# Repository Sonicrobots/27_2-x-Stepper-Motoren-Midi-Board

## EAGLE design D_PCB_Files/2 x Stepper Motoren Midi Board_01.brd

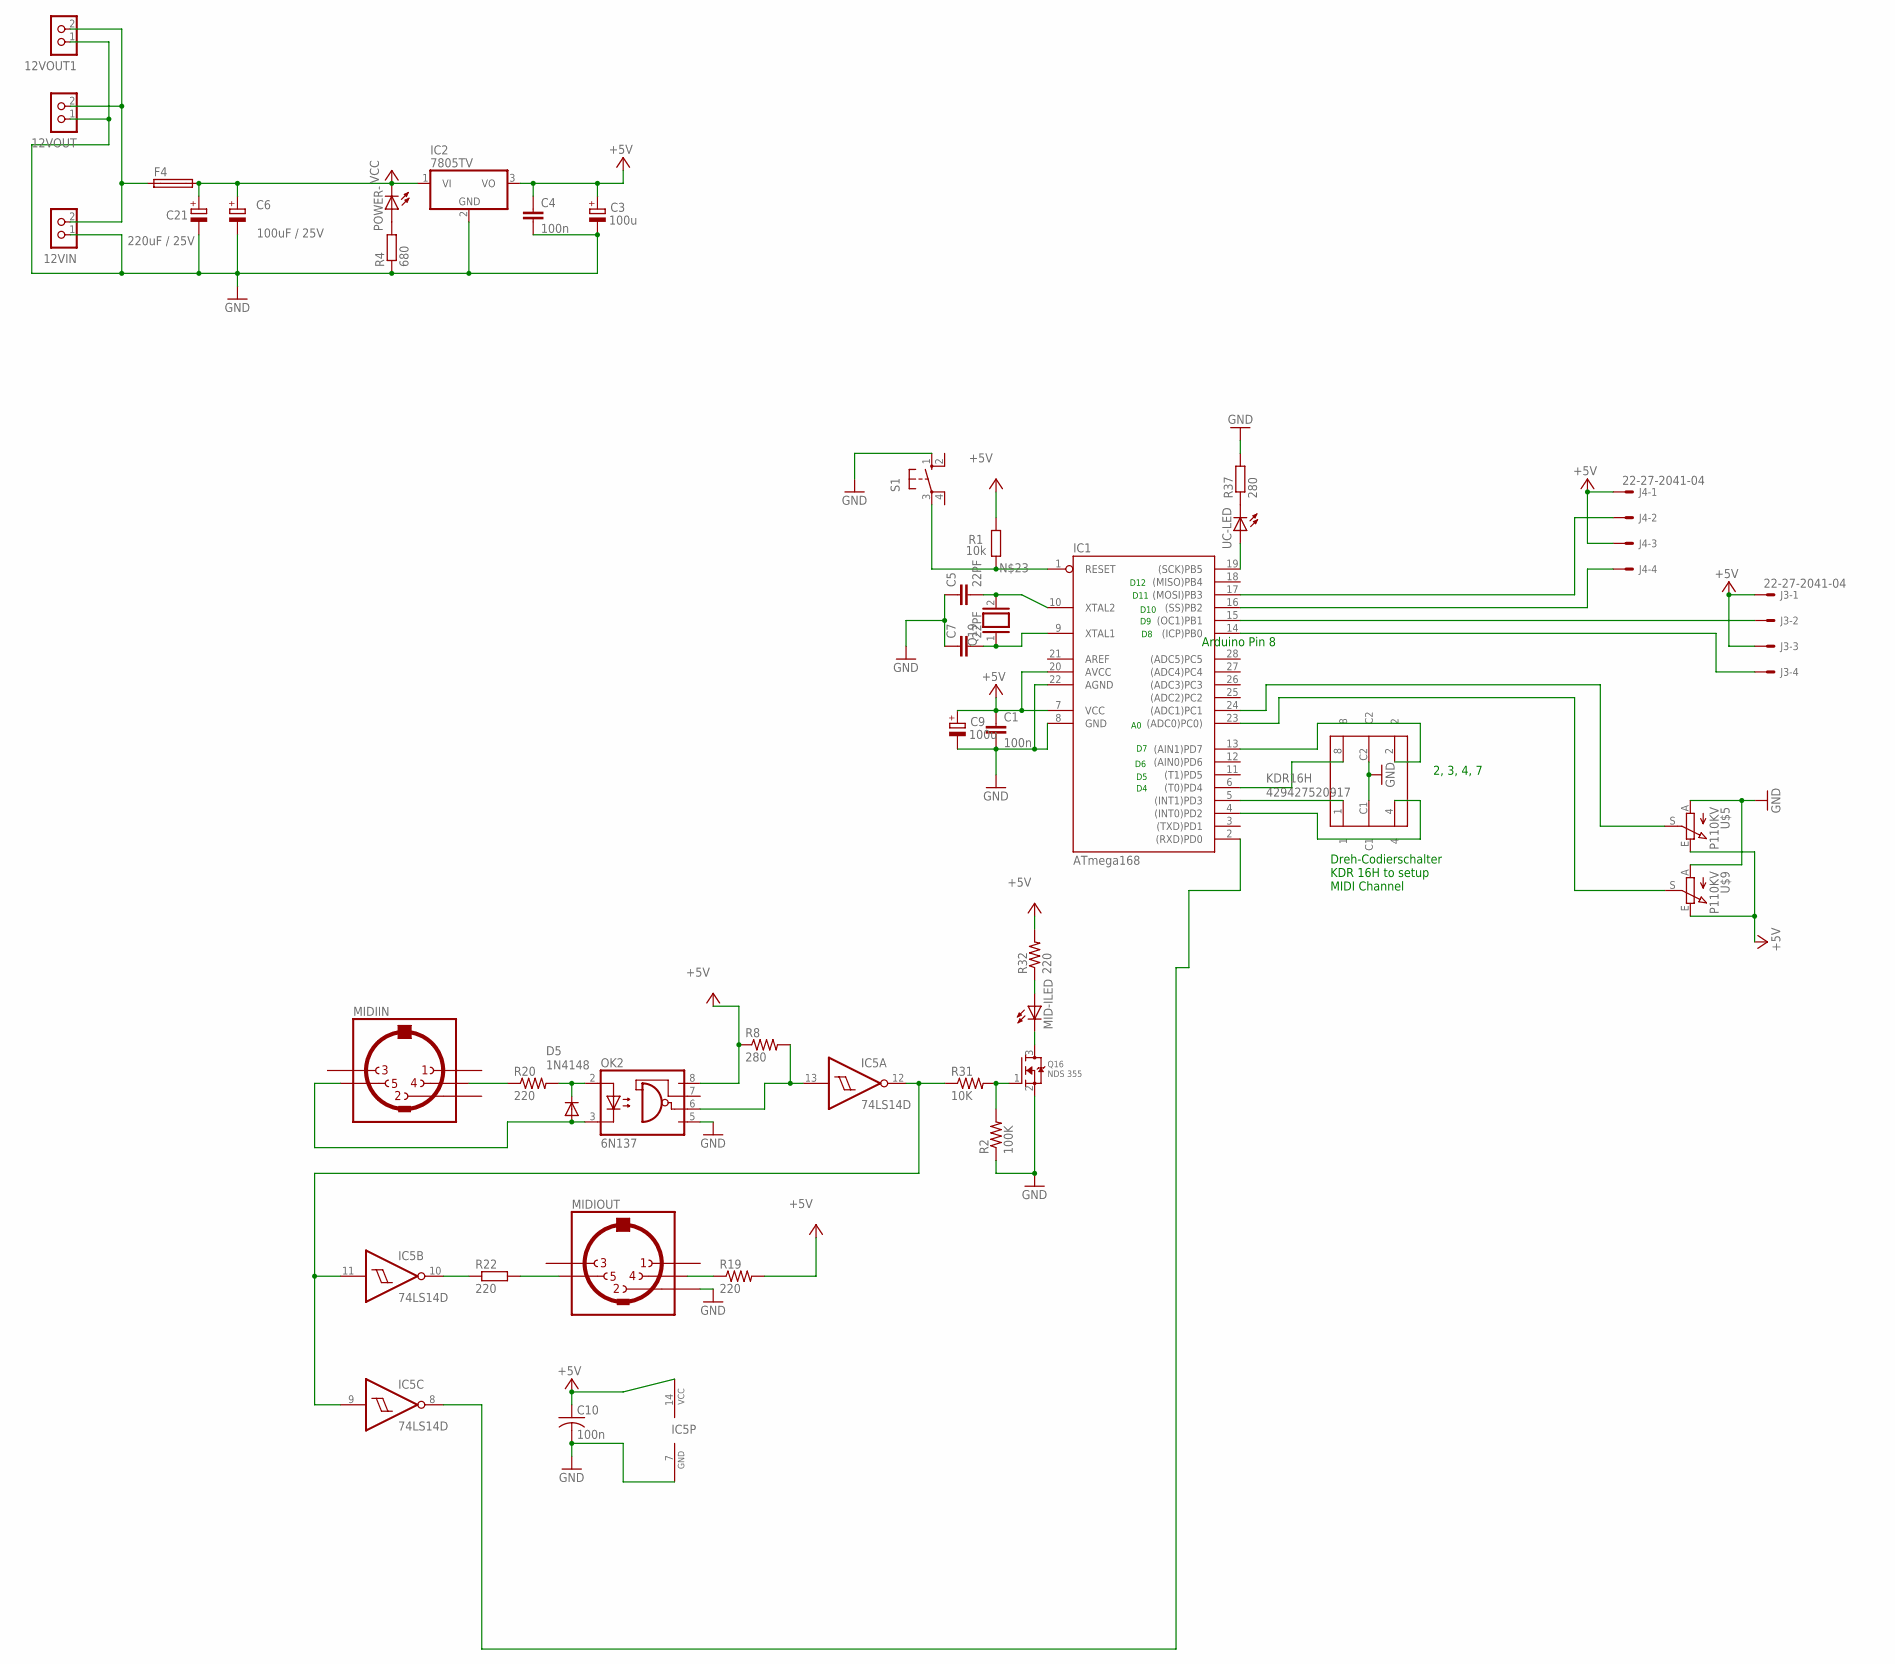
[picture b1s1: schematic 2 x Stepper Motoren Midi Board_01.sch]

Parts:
12VIN, 12VOUT, 12VOUT1: CON_TERMINAL_BLOCK_02-5MM; TERMINAL_BLOCK_2P_5
C1, C4: 100n; C0805K
C3: 100u; E2,5-7
C5, C7: 22PF; C0805
C6: 100uF / 25V; E2,5-7
C9: 100u; E2,5-6
C10: 100n; C0805
C21: 220uF / 25V; E5-8,5
D5: 1N4148; D-7.5
F4: SH22,5
IC1: ATmega168; DIL28-3
IC2: 7805TV; TO220V
IC5: 74LS14D; SO14
J3, J4: 22-27-2041-04; 6410-04
KDR16H: 429427520917
MID-ILED: LED3MM
MIDIIN: MAB5SH
MIDIOUT: MAB5SH
OK2: 6N137; DIL08; MPN 6N137
POWER-: LED3MM
Q16: NDS 355; SOT23-W
Q19: XTAL/S; QS
R1: 10k; R0805
R2: 100K; R0805W
R4: 680; R0805W
R8: 280; M0805
R19, R32: 220; R0805W
R20, R22: 220; R0805
R31: 10K; R0805W
R37: 280; R0805
S1: 10-XX; B3F-10XX
U$5, U$9: P110KV; POT-P110KV
UC-LED: LED3MM

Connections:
+5V: C1.1, C3.+, C4.1, C9.+, C10.1, IC1.7 (VCC), IC1.20 (AVCC), IC2.3 (VO), IC5.14 (VCC), J3.1, J3.3, J4.1, J4.3, OK2.8 (VCC), R1.2, R8.1, R19.2, R32.2, U$5.E, U$9.E
A1_IN: IC1.24 ((ADC1)PC1), U$5.S
A2_IN: IC1.23 ((ADC0)PC0)), U$9.S
GND: 12VIN.1, 12VOUT.1, 12VOUT1.1, C1.2, C3.-, C4.2, C5.1, C6.-, C7.1, C9.-, C10.2, C21.-, IC1.8 (GND), IC1.22 (AGND), IC2.2 (GND), IC5.7 (GND), KDR16H.C1, KDR16H.C2, MIDIOUT.2, OK2.5 (GND), Q16.2 (S), R2.1, R4.1, R37.2, S1.1 (S), U$5.A, U$9.A
MIDI_IN1: IC5.9 (I), IC5.11 (I), IC5.12 (O), R31.1
unnamed: IC1.15 ((OC1)PB1), J3.2
unnamed: IC1.14 ((ICP)PB0), J3.4
unnamed: POWER-.A, R4.2
unnamed: IC1.16 ((SS)PB2), J4.4
unnamed: 12VIN.2, 12VOUT.2, 12VOUT1.2, F4.1
unnamed: C7.2, IC1.9 (XTAL1), Q19.1
unnamed: C5.2, IC1.10 (XTAL2), Q19.2
unnamed: IC1.17 ((MOSI)PB3), J4.2
unnamed: IC1.1 (RESET), R1.1, S1.3
unnamed: IC1.2 ((RXD)PD0), IC5.8 (O)
unnamed: MIDIOUT.4, R19.1
unnamed: IC5.13 (I), OK2.6 (VO), R8.2
unnamed: D5.A, MIDIIN.5, OK2.3 (C)
unnamed: D5.C, OK2.2 (A), R20.2
unnamed: IC5.10 (O), R22.1
unnamed: MIDIOUT.5, R22.2
unnamed: R37.1, UC-LED.K (C)
unnamed: Q16.1 (G), R2.2, R31.2
unnamed: MID-ILED.K (C), Q16.3 (D)
unnamed: MID-ILED.A, R32.1
unnamed: MIDIIN.4, R20.1
unnamed: IC1.19 ((SCK)PB5), UC-LED.A
unnamed: IC1.13 ((AIN1)PD7), KDR16H.2
unnamed: IC1.6 ((T0)PD4), KDR16H.8
unnamed: IC1.5 ((INT1)PD3), KDR16H.1
unnamed: IC1.4 ((INT0)PD2), KDR16H.4
VCC: C6.+, C21.+, F4.2, IC2.1 (VI), POWER-.K (C)

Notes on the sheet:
Arduino Pin 8
Dreh-Codierschalter KDR 16H to setup MIDI Channel
D10
D11
D12
2, 3, 4, 7

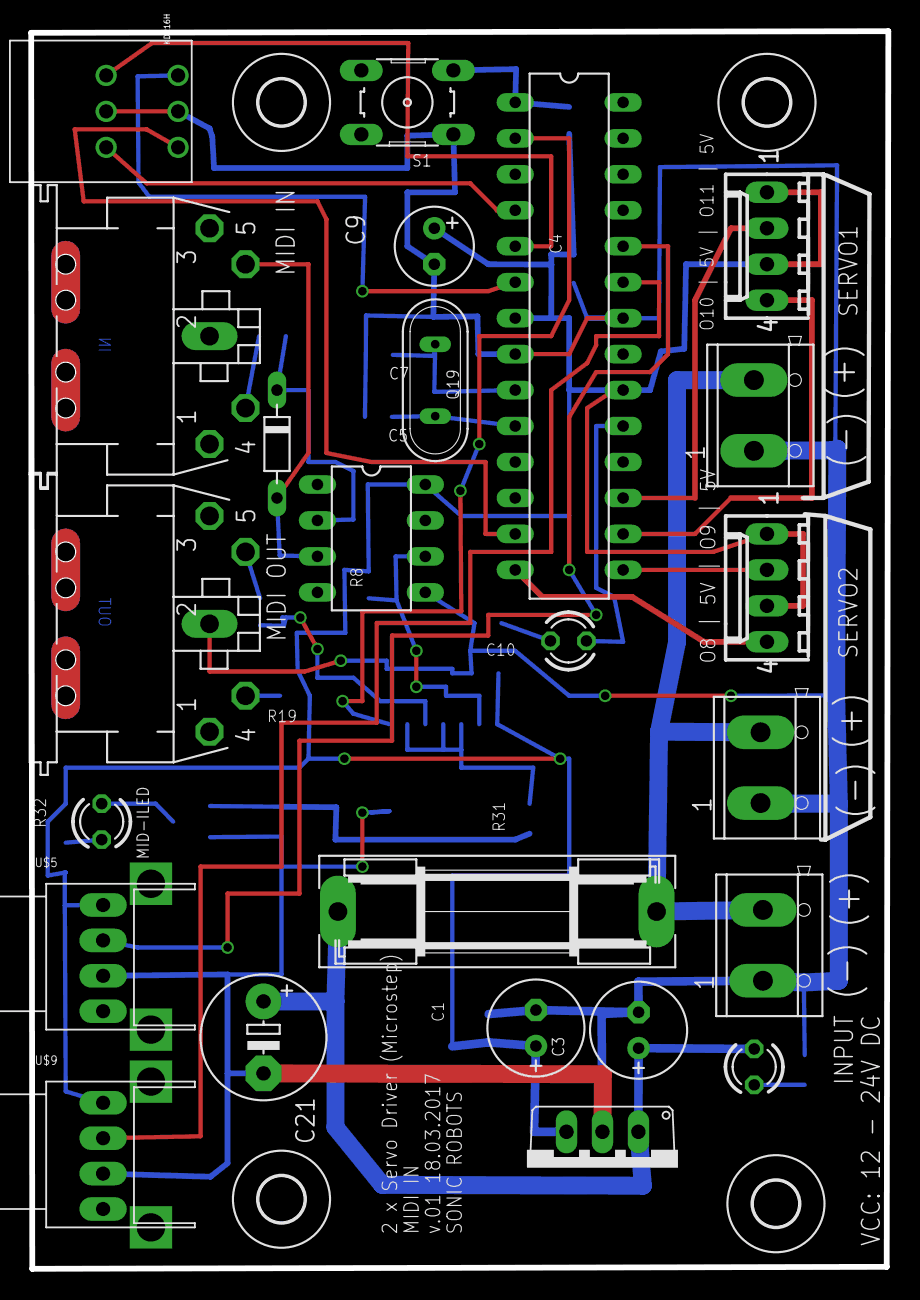
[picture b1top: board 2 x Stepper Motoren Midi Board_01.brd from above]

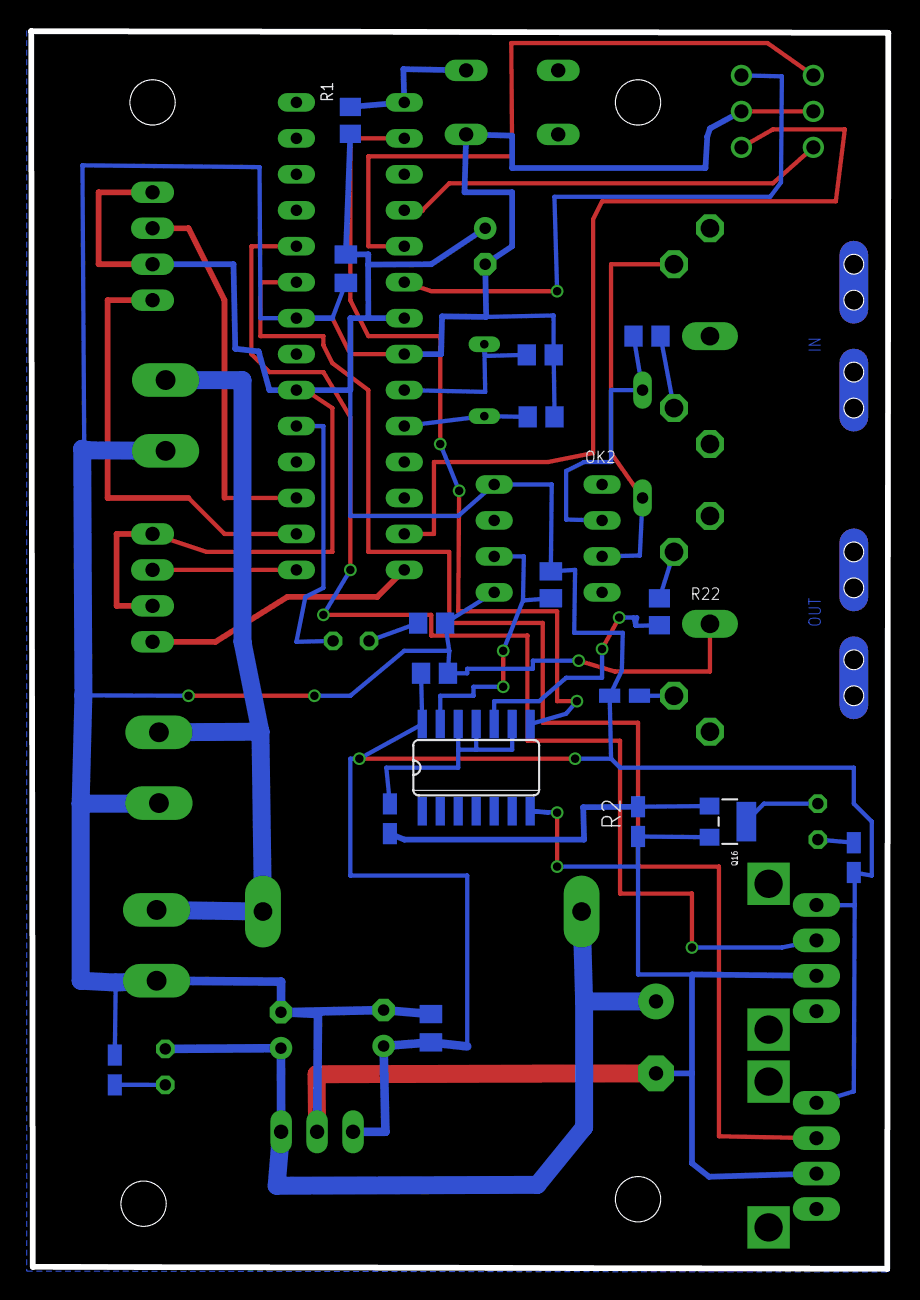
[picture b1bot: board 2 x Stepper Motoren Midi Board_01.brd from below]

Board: 2 copper layers, 60.5 x 87.4 mm, 45 parts (17 on the bottom side), 32 nets.

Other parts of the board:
U$2, U$3, U$4, U$6: 3,2

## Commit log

2017-05-08 :lollipop: Added .gitattributes & .gitignore files
2017-05-08 first issue
2017-05-08 PDF Docu added
2017-05-08 Unused files Deleted

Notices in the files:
parts and their libraries:
Eagle_Wuerth_Elektronik_Switch: Copyright: Würth Elektronik
